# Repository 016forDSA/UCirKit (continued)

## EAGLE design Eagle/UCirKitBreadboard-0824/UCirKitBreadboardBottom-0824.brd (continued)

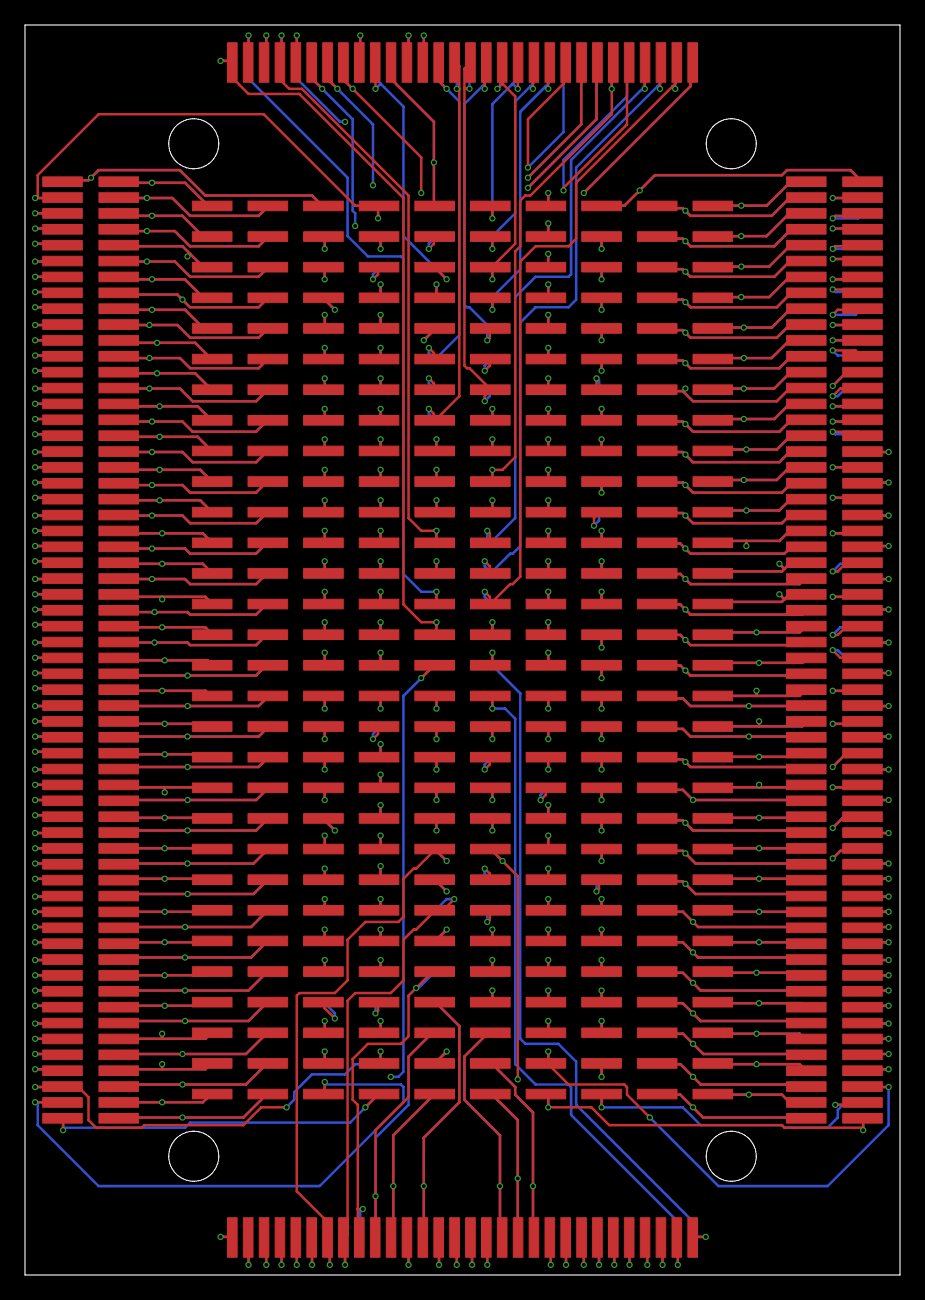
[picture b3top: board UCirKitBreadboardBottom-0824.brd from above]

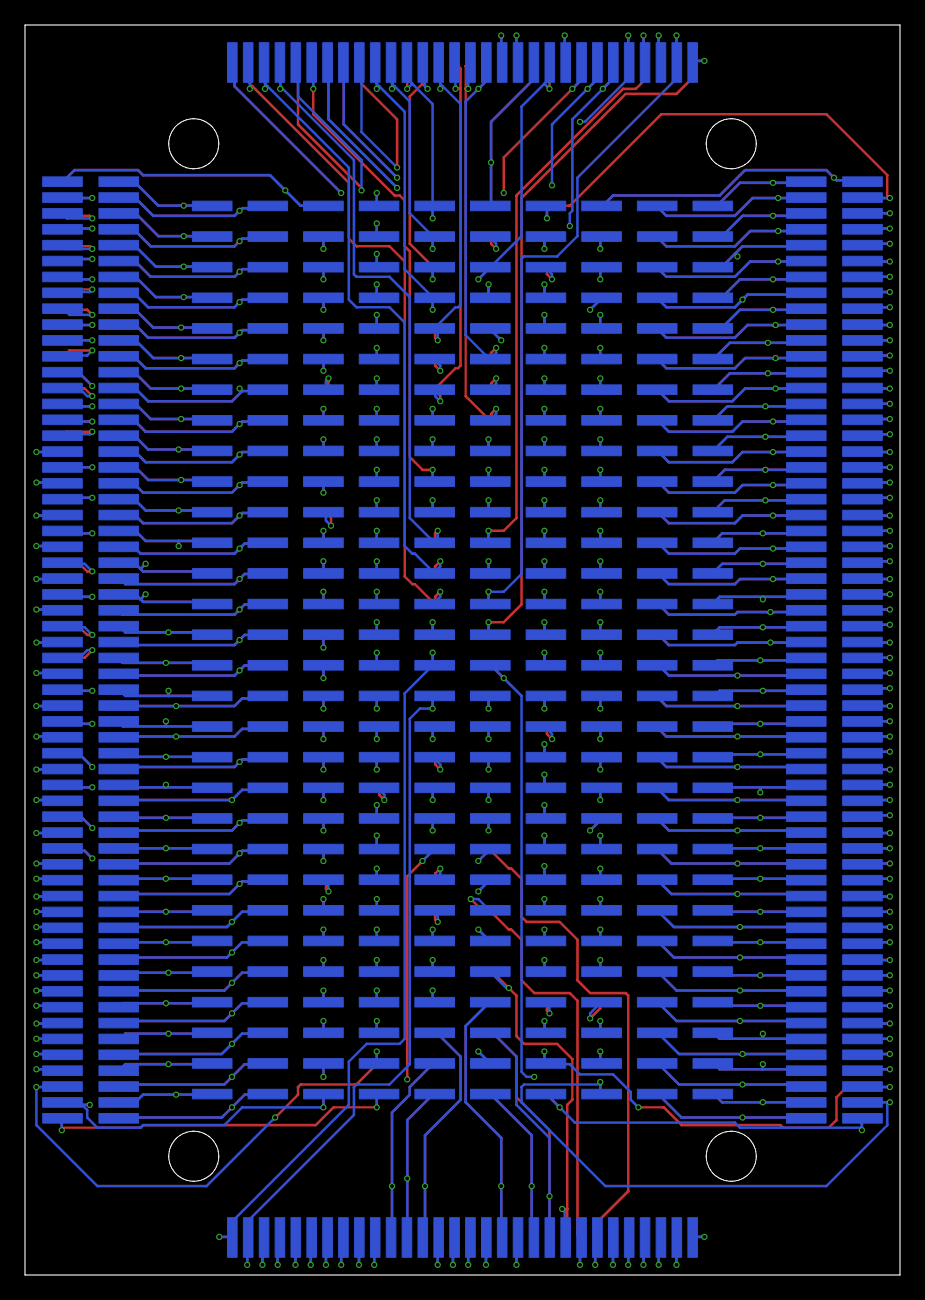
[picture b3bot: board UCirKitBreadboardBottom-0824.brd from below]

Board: 4 copper layers, 70.0 x 100.0 mm, 1200 parts (600 on the bottom side), 300 nets.

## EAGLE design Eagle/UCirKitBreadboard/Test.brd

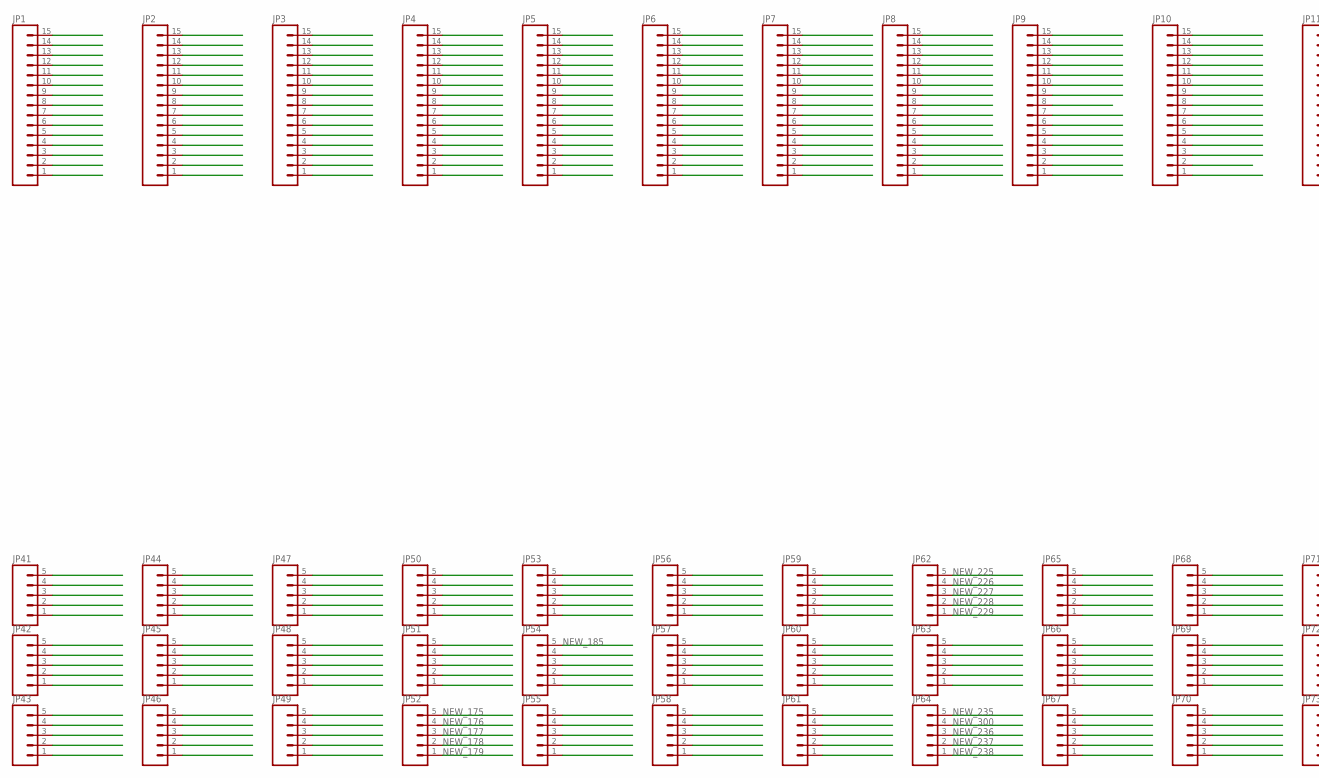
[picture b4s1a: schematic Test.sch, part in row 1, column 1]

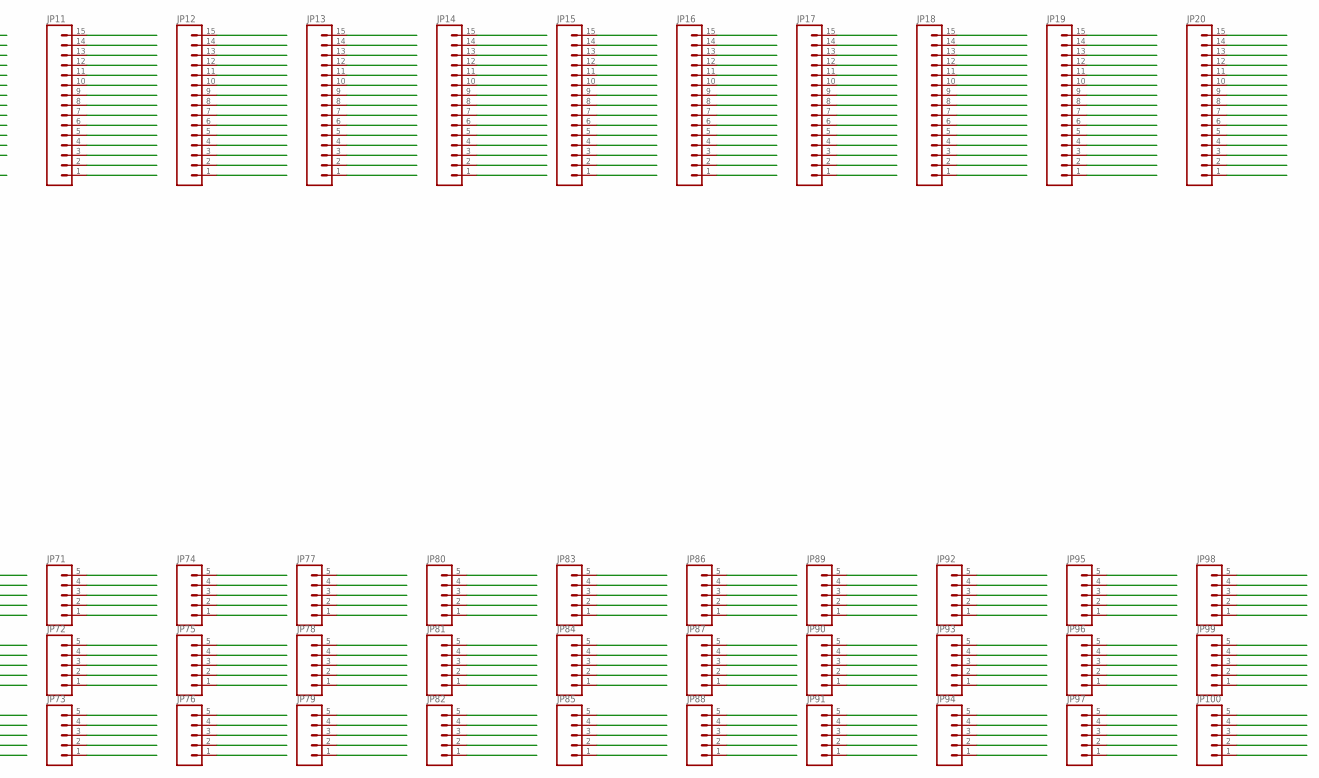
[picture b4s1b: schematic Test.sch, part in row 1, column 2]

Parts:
JP1, JP2, JP3, JP4, JP5, JP6, JP7, JP8, JP9, JP10, JP11, JP12, JP13, JP14, JP15, JP16, JP17, JP18, JP19, JP20: M15; 1X15
JP41, JP42, JP43, JP44, JP45, JP46, JP47, JP48, JP49, JP50, JP51, JP52, JP53, JP54, JP55, JP56, JP57, JP58, JP59, JP60, JP61, JP62, JP63, JP64, JP65, JP66, JP67, JP68, JP69, JP70, JP71, JP72, JP73, JP74, JP75, JP76, JP77, JP78, JP79, JP80, JP81, JP82, JP83, JP84, JP85, JP86, JP87, JP88, JP89, JP90, JP91, JP92, JP93, JP94, JP95, JP96, JP97, JP98, JP99, JP100: M051.27MM; 1X05-1.27MM

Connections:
NEW_0: JP7.3, JP65.5
NEW_1: JP7.2, JP65.4
NEW_2: JP8.2, JP65.3
NEW_3: JP7.1, JP65.2
NEW_4: JP8.1, JP65.1
NEW_5: JP7.5, JP66.5
NEW_6: JP8.5, JP66.4
NEW_7: JP7.4, JP66.3
NEW_8: JP8.4, JP66.2
NEW_9: JP8.3, JP66.1
NEW_10: JP7.8, JP67.5
NEW_11: JP7.7, JP67.4
NEW_12: JP8.7, JP67.3
NEW_13: JP7.6, JP67.2
NEW_14: JP8.6, JP67.1
NEW_15: JP7.10, JP68.5
NEW_16: JP8.10, JP68.4
NEW_17: JP7.9, JP68.3
NEW_18: JP8.9, JP68.2
NEW_19: JP8.8, JP68.1
NEW_20: JP7.13, JP69.5
NEW_21: JP7.12, JP69.4
NEW_22: JP8.12, JP69.3
NEW_23: JP7.11, JP69.2
NEW_24: JP8.11, JP69.1
NEW_25: JP7.15, JP70.5
NEW_26: JP8.15, JP70.4
NEW_27: JP7.14, JP70.3
NEW_28: JP8.14, JP70.2
NEW_29: JP8.13, JP70.1
NEW_30: JP17.3, JP71.5
NEW_31: JP17.2, JP71.4
NEW_32: JP18.2, JP71.3
NEW_33: JP17.1, JP71.2
NEW_34: JP18.1, JP71.1
NEW_35: JP17.5, JP72.5
NEW_36: JP18.5, JP72.4
NEW_37: JP17.4, JP72.3
NEW_38: JP18.4, JP72.2
NEW_39: JP18.3, JP72.1
NEW_40: JP17.8, JP73.5
NEW_41: JP17.7, JP73.4
NEW_42: JP18.7, JP73.3
NEW_43: JP17.6, JP73.2
NEW_44: JP18.6, JP73.1
NEW_45: JP17.10, JP74.5
NEW_46: JP18.10, JP74.4
NEW_47: JP17.9, JP74.3
NEW_48: JP18.9, JP74.2
NEW_49: JP18.8, JP74.1
NEW_50: JP17.13, JP75.5
NEW_51: JP17.12, JP75.4
NEW_52: JP18.12, JP75.3
NEW_53: JP17.11, JP75.2
NEW_54: JP18.11, JP75.1
NEW_55: JP17.15, JP76.5
NEW_56: JP18.15, JP76.4
NEW_57: JP17.14, JP76.3
NEW_58: JP18.14, JP76.2
NEW_59: JP18.13, JP76.1
NEW_60: JP9.3, JP77.5
NEW_61: JP9.2, JP77.4
NEW_62: JP10.2, JP77.3
NEW_63: JP9.1, JP77.2
NEW_64: JP10.1, JP77.1
NEW_65: JP9.5, JP78.5
NEW_66: JP10.5, JP78.4
NEW_67: JP9.4, JP78.3
NEW_68: JP10.4, JP78.2
NEW_69: JP10.3, JP78.1
NEW_70: JP9.8, JP79.5
NEW_71: JP9.7, JP79.4
NEW_72: JP10.7, JP79.3
NEW_73: JP9.6, JP79.2
NEW_74: JP10.6, JP79.1
NEW_75: JP9.10, JP80.5
NEW_76: JP10.10, JP80.4
NEW_77: JP9.9, JP80.3
NEW_78: JP10.9, JP80.2
NEW_79: JP10.8, JP80.1
NEW_80: JP9.13, JP81.5
NEW_81: JP9.12, JP81.4
NEW_82: JP10.12, JP81.3
NEW_83: JP9.11, JP81.2
NEW_84: JP10.11, JP81.1
NEW_85: JP9.15, JP82.5
NEW_86: JP10.15, JP82.4
NEW_87: JP9.14, JP82.3
NEW_88: JP10.14, JP82.2
NEW_89: JP10.13, JP82.1
NEW_90: JP19.3, JP83.5
NEW_91: JP19.2, JP83.4
NEW_92: JP20.2, JP83.3
NEW_93: JP19.1, JP83.2
NEW_94: JP20.1, JP83.1
NEW_95: JP19.5, JP84.5
NEW_96: JP20.5, JP84.4
NEW_97: JP19.4, JP84.3
NEW_98: JP20.4, JP84.2
NEW_99: JP20.3, JP84.1
NEW_100: JP19.8, JP85.5
NEW_101: JP19.7, JP85.4
NEW_102: JP20.7, JP85.3
NEW_103: JP19.6, JP85.2
NEW_104: JP20.6, JP85.1
NEW_105: JP19.10, JP86.5
NEW_106: JP20.10, JP86.4
NEW_107: JP19.9, JP86.3
NEW_108: JP20.9, JP86.2
NEW_109: JP20.8, JP86.1
NEW_110: JP19.13, JP87.5
NEW_111: JP19.12, JP87.4
NEW_112: JP20.12, JP87.3
NEW_113: JP19.11, JP87.2
NEW_114: JP20.11, JP87.1
NEW_115: JP19.15, JP88.5
NEW_116: JP20.15, JP88.4
NEW_117: JP19.14, JP88.3
NEW_118: JP20.14, JP88.2
NEW_119: JP20.13, JP88.1
NEW_120: JP1.3, JP41.5
NEW_121: JP1.2, JP41.4
NEW_122: JP2.2, JP41.3
NEW_123: JP1.1, JP41.2
NEW_124: JP2.1, JP41.1
NEW_125: JP1.5, JP42.5
NEW_126: JP2.5, JP42.4
NEW_127: JP1.4, JP42.3
NEW_128: JP2.4, JP42.2
NEW_129: JP2.3, JP42.1
NEW_130: JP1.8, JP43.5
NEW_131: JP1.7, JP43.4
NEW_132: JP2.7, JP43.3
NEW_133: JP1.6, JP43.2
NEW_134: JP2.6, JP43.1
NEW_135: JP1.10, JP44.5
NEW_136: JP2.10, JP44.4
NEW_137: JP1.9, JP44.3
NEW_138: JP2.9, JP44.2
NEW_139: JP2.8, JP44.1
NEW_140: JP1.13, JP45.5
NEW_141: JP1.12, JP45.4
NEW_142: JP2.12, JP45.3
NEW_143: JP1.11, JP45.2
NEW_144: JP2.11, JP45.1
NEW_145: JP1.15, JP46.5
NEW_146: JP2.15, JP46.4
NEW_147: JP1.14, JP46.3
NEW_148: JP2.14, JP46.2
NEW_149: JP2.13, JP46.1
NEW_150: JP11.3, JP47.5
NEW_151: JP11.2, JP47.4
NEW_152: JP12.2, JP47.3
NEW_153: JP11.1, JP47.2
NEW_154: JP12.1, JP47.1
NEW_155: JP11.5, JP48.5
NEW_156: JP12.5, JP48.4
NEW_157: JP11.4, JP48.3
NEW_158: JP12.4, JP48.2
NEW_159: JP12.3, JP48.1
NEW_160: JP11.8, JP49.5
NEW_161: JP11.7, JP49.4
NEW_162: JP12.7, JP49.3
NEW_163: JP11.6, JP49.2
NEW_164: JP12.6, JP49.1
NEW_165: JP11.10, JP50.5
NEW_166: JP12.10, JP50.4
NEW_167: JP11.9, JP50.3
NEW_168: JP12.9, JP50.2
NEW_169: JP12.8, JP50.1
NEW_170: JP11.13, JP51.5
NEW_171: JP11.12, JP51.4
NEW_172: JP12.12, JP51.3
NEW_173: JP11.11, JP51.2
NEW_174: JP12.11, JP51.1
NEW_175: JP11.15, JP52.5
NEW_176: JP12.15, JP52.4
NEW_177: JP11.14, JP52.3
NEW_178: JP12.14, JP52.2
NEW_179: JP12.13, JP52.1
NEW_180: JP3.3, JP53.5
NEW_181: JP3.2, JP53.4
NEW_182: JP4.2, JP53.3
NEW_183: JP3.1, JP53.2
NEW_184: JP4.1, JP53.1
NEW_185: JP3.5, JP54.5
NEW_186: JP4.5, JP54.4
NEW_187: JP3.4, JP54.3
NEW_188: JP4.4, JP54.2
NEW_189: JP4.3, JP54.1
NEW_190: JP3.8, JP55.5
NEW_191: JP3.7, JP55.4
NEW_192: JP4.7, JP55.3
NEW_193: JP3.6, JP55.2
NEW_194: JP4.6, JP55.1
NEW_195: JP3.10, JP56.5
NEW_196: JP4.10, JP56.4
NEW_197: JP3.9, JP56.3
NEW_198: JP4.9, JP56.2
NEW_199: JP4.8, JP56.1
NEW_200: JP3.13, JP57.5
NEW_201: JP3.12, JP57.4
NEW_202: JP4.12, JP57.3
NEW_203: JP3.11, JP57.2
NEW_204: JP4.11, JP57.1
NEW_205: JP3.15, JP58.5
NEW_206: JP4.15, JP58.4
NEW_207: JP3.14, JP58.3
NEW_208: JP4.14, JP58.2
NEW_209: JP4.13, JP58.1
NEW_210: JP13.3, JP59.5
NEW_211: JP13.2, JP59.4
NEW_212: JP14.2, JP59.3
NEW_213: JP13.1, JP59.2
NEW_214: JP14.1, JP59.1
NEW_215: JP13.5, JP60.5
NEW_216: JP14.5, JP60.4
NEW_217: JP13.4, JP60.3
NEW_218: JP14.4, JP60.2
NEW_219: JP14.3, JP60.1
NEW_220: JP13.8, JP61.5
NEW_221: JP13.7, JP61.4
NEW_222: JP14.7, JP61.3
NEW_223: JP13.6, JP61.2
NEW_224: JP14.6, JP61.1
NEW_225: JP13.10, JP62.5
NEW_226: JP14.10, JP62.4
NEW_227: JP13.9, JP62.3
NEW_228: JP14.9, JP62.2
NEW_229: JP14.8, JP62.1
NEW_230: JP13.13, JP63.5
NEW_231: JP13.12, JP63.4
NEW_232: JP14.12, JP63.3
NEW_233: JP13.11, JP63.2
NEW_234: JP14.11, JP63.1
NEW_235: JP14.15, JP64.5
NEW_236: JP13.14, JP64.3
NEW_237: JP14.14, JP64.2
NEW_238: JP14.13, JP64.1
NEW_239: JP5.5, JP89.5
NEW_240: JP5.4, JP89.4
NEW_241: JP5.3, JP89.3
NEW_242: JP5.2, JP89.2
NEW_243: JP5.1, JP89.1
NEW_244: JP5.10, JP90.5
NEW_245: JP5.9, JP90.4
NEW_246: JP5.8, JP90.3
NEW_247: JP5.7, JP90.2
NEW_248: JP5.6, JP90.1
NEW_249: JP5.15, JP91.5
NEW_250: JP5.14, JP91.4
NEW_251: JP5.13, JP91.3
NEW_252: JP5.12, JP91.2
NEW_253: JP5.11, JP91.1
NEW_254: JP15.5, JP92.5
NEW_255: JP15.4, JP92.4
NEW_256: JP15.3, JP92.3
NEW_257: JP15.2, JP92.2
NEW_258: JP15.1, JP92.1
NEW_259: JP15.11, JP97.5
NEW_260: JP15.12, JP97.4
NEW_261: JP15.13, JP97.3
NEW_262: JP15.14, JP97.2
NEW_263: JP15.15, JP97.1
NEW_264: JP15.6, JP98.5
NEW_265: JP15.7, JP98.4
NEW_266: JP15.8, JP98.3
NEW_267: JP15.9, JP98.2
NEW_268: JP15.10, JP98.1
NEW_269: JP16.1, JP93.5
NEW_270: JP16.2, JP93.4
NEW_271: JP16.3, JP93.3
NEW_272: JP16.4, JP93.2
NEW_273: JP16.5, JP93.1
NEW_274: JP6.11, JP94.5
NEW_275: JP6.12, JP94.4
NEW_276: JP6.13, JP94.3
NEW_277: JP6.14, JP94.2
NEW_278: JP6.15, JP94.1
NEW_279: JP6.6, JP95.5
NEW_280: JP6.7, JP95.4
NEW_281: JP6.8, JP95.3
NEW_282: JP6.9, JP95.2
NEW_283: JP6.10, JP95.1
NEW_284: JP6.1, JP96.5
NEW_285: JP6.2, JP96.4
NEW_286: JP6.3, JP96.3
NEW_287: JP6.4, JP96.2
NEW_288: JP6.5, JP96.1
NEW_289: JP16.10, JP99.5
NEW_290: JP16.9, JP99.4
NEW_291: JP16.8, JP99.3
NEW_292: JP16.7, JP99.2
NEW_293: JP16.6, JP99.1
NEW_294: JP16.15, JP100.5
NEW_295: JP16.14, JP100.4
NEW_296: JP16.13, JP100.3
NEW_297: JP16.12, JP100.2
NEW_298: JP16.11, JP100.1
NEW_300: JP13.15, JP64.4

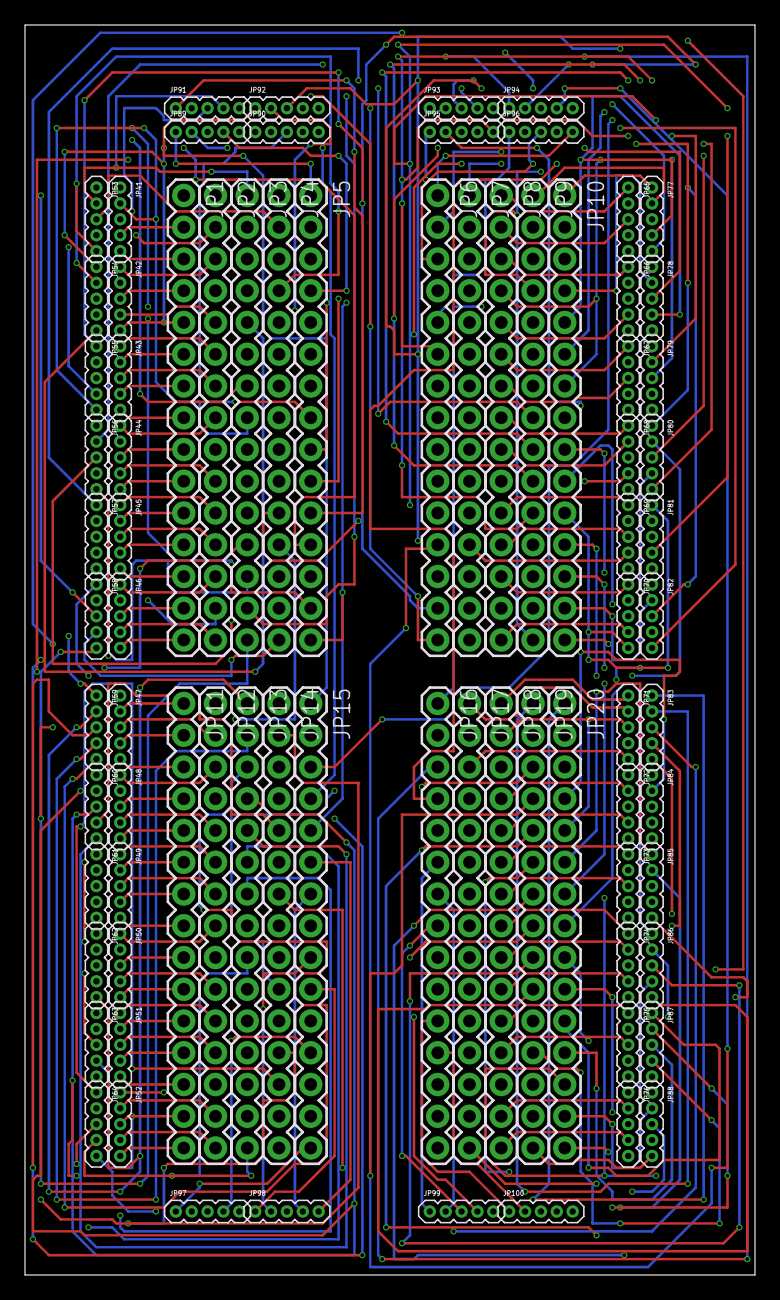
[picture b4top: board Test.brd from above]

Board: 4 copper layers, 58.4 x 100.0 mm, 80 parts (0 on the bottom side), 300 nets.
